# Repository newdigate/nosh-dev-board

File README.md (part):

# Nosh

A development board for the NXP **i.MX RT1176** crossover MCU, modelled closely on the
MIMXRT1170-EVKB (Rev C3) so that EVKB software — `USBHost_t36`, the M2Radio Wi-Fi/BT
library, `MipiDisplay` and the NXP SDK board files — runs with the same pin assignments.
Where Nosh departs from the EVKB it is for JLCPCB availability or because an EVKB block was
not wanted; every departure is listed below.

**Status:** schematic and PCB layout complete (KiCad 10, `Kicad/`): 6-layer JLCPCB stackup, fully
routed, DRC clean with schematic parity. The findings of the 2026-10-28 design review are closed
and merged to `main` on 2026-11-03 (decoupling moved to the chips, DC-jack OVP, reset supervisor,
RTC load caps, MIPI pair matching, ESD on the jacks, P-FET reverse-polarity switch and the rest;
see the git log). ERC is clean apart from the expected unconnected MCU balls and undriven-input
notes on open pins. The JLCPCB order files are in `fab/`; see [Fabrication outputs](#fabrication-outputs).
Ordered 2026-11-03: JLCPCB Y95-2611336A, 5 PCBs + 2 assembled (settings in `fab/README.md`).

## What is on the board

| Block | Choice | Notes |
|---|---|---|
| MCU | MIMXRT1176DVMAA (rev-B DVMAB accepted alternate), MAPBGA-289 | 12-unit symbol generated from `tools/data/*.json`; KiCad stock footprint `Package_BGA:MAPBGA-289_14x14mm_Layout17x17_P0.8mm` (0.32 mm pads, EVKB uses 0.33 mm) |
| SDRAM | 2 × Alliance AS4C32M16SC-7TIN (512 Mb, 133 MHz) on SEMC, 32-bit, **128 MB** | same JEDEC x16 TSOP-54 footprint and arrangement as the EVKB; 13 row × 10 column and a -7 speed grade, so the firmware SEMC setup changes: 10 column bits, 128 MB on chip select 0 and a 132 MHz SEMC clock, see "SDRAM configuration" below |
| Flash | Winbond W25Q512JVEIQ, 512 Mb QSPI, 3.3 V | FlexSPI1 port A (GPIO_SD_B2_06..11) |
| USB2 (OTG2) | micro-AB **host/OTG** port | the port `USBHost_t36` drives; TPS2553 VBUS switch (~1.1 A) with hardware ID gating, RClamp0854P ESD, low-DCR 120 Ω VBUS bead; ≈4.6 V at the connector when sourcing 1 A from the jack |
| USB1 (OTG1) | USB-C **device** port | Rd-only UFP (500 mA), RClamp0854P ESD |
| M.2 Key E | uSDHC1 @ 1.8 V + LPUART2 | for u-blox MAYA-W1 / NXP IW416; 74AVC8T245 level shifters; TE 2199230-4 socket (EVKB part); retention nut H5, M2.5 SMT 2 mm (EVKB BH1) |
| microSD | uSDHC2 @ 3.3 V, TPD1E05U06 ESD diode on each of the six lines | its own bus — the EVKB shares one with the M.2 slot |
| LCD + touch | 40-pin 0.5 mm FPC (Würth 68714014022), MIPI DSI 2 lanes | Rocktech RK055HDMIPI4MA0 (720×1280, HX8394, GT911 touch on LPI2C5), EVKB J48 pinout and GPIO map |
| Audio | NXP SGTL5000 codec (QFN-20) on SAI1 + LPI2C5, 3.5 mm line-out and line-in jacks with TPD1E10B06 bidirectional ESD on the jack side of the coupling caps | the Teensy Audio Shield codec: Teensy Audio library `AudioControlSGTL5000` and the NXP SDK `sgtl5000` driver both apply; I2C 0x0A; same SAI1 pins as the EVKB codec |
| Power | 5 V barrel jack or USB-C → MP2143 3.3 V buck → TLV1117LV 1.8 V; AP2112K SNVS LDO | EVKB-style rail tree, on-chip DCDC for the core; 3 A polyfuse, SMAJ6.0A TVS, IRLML6401 P-FET reverse-polarity switch (gate to GND, ~50 mΩ; replaced the SS54 diode 2026-11-02 to lift the host-port VBUS), TPS259531 eFuse (5.7 V clamp, 3.6 A limit), jack rated 8 A; red power LED on +3V3 |
| Debug | 10-pin 1.27 mm SWD/JTAG header, reset / ONOFF / WAKEUP buttons, 2-way boot-mode DIP, user LED on GPIO_AD_04, 3-pin debug UART header J11 | JTAG on GPIO_LPSR_10..15, VTref = NVCC_LPSR (3.3 V); LPUART1 console on J11 |
| Expansion | none | the 2×10 header J10 was taken off during layout (commit a9f1b1f) to free routing room; see [Expansion header (removed)](#expansion-header-removed) |
| Mechanical | board outline = the RK055HDMIPI4MA0 adapter outline; 4 × M3 mounting holes H1–H4 on the adapter's standoff positions; 6 fiducials, FID1–FID3 on the top side and FID4–FID6 on the bottom for the bottom-side assembly pass | 3.53 mm plated holes with 5.6 mm GND pads (NXP's .635" M3 standoff land, as on the EVKB); hole coordinates from the adapter design files or measurement before layout |

Sheets: `power` (MCU supplies, DCDC, reset/boot), `core` (crystals, USB/MIPI supplies),
`gpio` (GPIO banks, flash, SWD, boot), `usb`, `supply`, `sdram`, `m2`, `sdcard`, `lcd`, `audio`.

## Pin map (for software)

All assignments are the EVKB's unless marked.

| Function | RT1176 pads / balls |
|---|---|
| USB host (OTG2) | USB2_DP/DN C17/C16, VBUS sense D16; `USB_OTG2_ID` GPIO_AD_08, `USB_OTG2_OC` GPIO_AD_06 |
| USB device (OTG1) | USB1_DP/DN E17/E16, VBUS sense D17 |
| M.2 SDIO (uSDHC1, 1.8 V) | GPIO_SD_B1_00..05; `WIFI_RST_B` GPIO_AD_16, `WL_RST_B` GPIO_AD_31, `BT_RST_B` GPIO_AD_15, `WL_DEV_WAKE` GPIO_AD_07, `BT_DEV_WAKE` GPIO_AD_28, `BT_WAKE_B` GPIO_AD_27, `WIFI_WAKE_B` GPIO_AD_29 |
| BT HCI UART (LPUART2) | GPIO_DISP_B2_10..13 |
| microSD (uSDHC2, 3.3 V) — *Nosh* | GPIO_SD_B2_00..05; `SD_CD_B` GPIO_AD_34, `SD_PWREN_B` GPIO_AD_35 |
| QSPI flash (FlexSPI1 A) | GPIO_SD_B2_06..11; read strobe (DQS) on GPIO_EMC_B2_18, see below |
| SDRAM (SEMC) | GPIO_EMC_B1/B2 |
| LCD (MIPI DSI) | D0 A8/B8, D1 A10/B10, CLK A9/B9; reset GPIO_AD_02, backlight GPIO_AD_30, panel power GPIO_DISP_B2_15, TE GPIO_AD_05 |
| Touch + codec I2C (LPI2C5) | GPIO_LPSR_04 SDA / GPIO_LPSR_05 SCL; touch INT GPIO_AD_00, touch RST GPIO_AD_01 |
| Audio (SAI1) | MCLK GPIO_AD_17, RX_SYNC/RX_BCLK GPIO_AD_18/19 (DNP links), RXD0 GPIO_AD_20, TXD0 GPIO_AD_21, TX_BCLK GPIO_AD_22, TX_SYNC GPIO_AD_23 |
| Boot mode | GPIO_LPSR_02/03 (DIP switch, 100 k pull-downs); BOOT_CFG pins GPIO_DISP_B1_06..11 / GPIO_DISP_B2_00..05 pulled down (100 k), so internal boot is from FlexSPI1 QSPI NOR |
| Debug console (LPUART1) | GPIO_AD_24 TXD / GPIO_AD_25 RXD on J11 (1 GND, 2 TXD, 3 RXD) |
| LPSPI3 — *Nosh* | not brought out (J10 removed); GPIO_DISP_B1_06 carries the BT_CFG0 strap (net LPSPI3_SOUT, R92), GPIO_DISP_B1_03..05 are unconnected |
| User LED | GPIO_AD_04 (GPIO9_IO03, the SDK's BOARD_USER_LED), high = on; direct drive, 1 k series, red 0603 (the EVKB buffers it with a BC817) |

## Expansion header (removed)

The 2×10 2.54 mm header J10 (LPUART1, LPI2C5, LPSPI3, FLEXCAN3/LPUART12, four ADC/PWM pins) was
taken off the board during layout (a9f1b1f, schematic cadd849) to free routing room around the
MCU. The pins it used are now unconnected and available if a header is ever added back:
GPIO_AD_10..13, GPIO_AD_26, GPIO_LPSR_00/01 (FLEXCAN3_TX/RX, PDM, MQS) and GPIO_DISP_B1_03..05.
GPIO_DISP_B1_06 (LPSPI3_SOUT) stays a boot strap (BOOT_CFG1[0], R92) and must not be pulled up.
NVCC_DISP1 is still 3.3 V. LPUART1 and LPI2C5 remain reachable on J11 and the LCD/codec nets.

## Differences from the MIMXRT1170-EVKB

| Block | EVKB | Nosh | Why |
|---|---|---|---|
| SDRAM | 2 × W9825G6KH-5I, 64 MB | 2 × AS4C32M16SC-7TIN, 128 MB | pin-compatible 512 Mb parts, 133 MHz (SEMC at 132 instead of 198 MHz); four ordered at JLCPCB on 2026-11-03 (C1349997) after the -6TIN pre-order (C1351095) stayed out of stock. W9825G6KH-6 (C62246, in stock) drops in for 64 MB at 166 MHz |
| USB ports | two micro-AB OTG ports | micro-AB host + USB-C device | one port is enough for the host library; USB-C for programming |
| USB VBUS switch | NX5P3090UK (0.4 mm WLCSP) | TPS2553DBVR (SOT-23-6), RILIM 22 k ≈ 1.1 A | no stock, hard package; same EN/FAULT/ILIM topology |
| SD card bus | shared with the M.2 slot | separate uSDHC2 | independent Wi-Fi and SD |
| M.2 BT HCI UART | needs NXP's "HCI UART rework" (mount the shifter-output 0 R links, cut the shared Arduino / Ethernet-PHY loads, set a jumper) | hard-wired, no rework | see below |
| QSPI flash | W25Q512NWEIQ (1.8 V) | W25Q512JVEIQ (3.3 V) | NVCC_SD2 at 3.3 V keeps the SD bus simple |
| NVCC_DISP1 | 1.8 V (RGMII Ethernet PHY on GPIO_DISP_B1) | 3.3 V | no Ethernet; the bank carries the BOOT_CFG / BT_CFG straps at 3.3 V |
| Boot configuration | DIP switch SW2 + 47 k pull-downs on the 12 BOOT_CFG pins | fixed 100 k pull-downs, no switch | always internal boot from QSPI NOR; reflash through the serial downloader (BOOT_MODE DIP) instead of changing boot devices |
| Arduino headers | four Arduino Uno R3 headers | none (J10 removed during layout) | the Arduino SPI pins (GPIO_AD_28..31) carry the M.2 and backlight signals here |
| LCD backlight / 2.8 V | on-board boost and LDO | none | the RK055HDMIPI4MA0 adapter (NXP SPF-39012) generates its own rails and drives its own backlight from the 5 V on FPC pins 39/40 — keep its jumpers J3/J5/J6 at the default 1-2 |
| LCD TE | 74AVC8T245 level shifter to GPIO_AD_05 | DNP 0 R | DSI video mode never uses TE; add a shifter if needed |
| Audio | WM8962 (0.5 mm WLCSP-49) with speaker outputs, electret mic and headphone jack with detect | SGTL5000 (QFN-20) with line out and line in | Teensy Audio library support; the QFN routes on standard 6-layer rules where the WLCSP needed via-in-pad; no mic, speakers or jack detect wanted |
| Not fitted at all | Ethernet (1G + 100M), CAN transceivers, camera, PMIC, LPC55 debug probe, PDM mics, accelerometer | — | use an external SWD probe; the FLEXCAN3 / PDM pins (GPIO_LPSR_00/01) are unconnected |

**No M.2 HCI UART rework.** NXP's EdgeFast Bluetooth
[hardware rework guide](https://mcuxpresso.nxp.com/mcuxsdk/25.09.00/html/middleware/edgefast_bluetooth/docs/HWRGEFBTPALUG/topics/RT1170EVKB_Murata_M2.html)
makes the EVKB + Murata M.2 combination work by mounting resistors, removing one and setting jumpers
(its designators are from an earlier EVKB build; on the RevC3 files the module-to-MCU UART_RXD/UART_CTS
links are R1901/R1902, 0 R DNP, and LPUART2's pins are shared with the Arduino header, the J57 FFC and
the Ethernet PHY reset/interrupt). Nosh needs none of it: GPIO_DISP_B2_10..13 run point-to-point through
U11/U12 (OE grounded, DIR fixed) to M.2 pins 32/22/36/34 with no 0 R links, no DNP parts and no other
loads, with the EVKB's pin mapping, so the SDK's LPUART2 flow-control setup applies unchanged. The guide's
PCM rework does not apply either: the M.2 PCM/I2S pins (8, 10, 12, 14) are not connected, so A2DP over
HCI works but HFP voice over the PCM path is not possible without a board change.

## Sourcing / BOM

The board is intended for JLCPCB assembly. Every component carries hidden `LCSC` and `MPN`
fields (U1 also `MPN_Alt`/`LCSC_Alt`), and `Kicad/tools/data/lcsc_parts.csv` is the generated
summary: one line per order code with quantity and references, DNP parts marked. Current count
(2026-11-03): 268 fitted parts on 70 order codes, 24 of them JLCPCB *Basic*; 8 DNP parts. Regenerate
it with

```bash
python3 Kicad/tools/lcsc_table.py
```

### Fabrication outputs

`fab/` holds the JLCPCB order files, regenerated from the board with

```bash
python3 Kicad/tools/fab_export.py
```

(`--no-tht` leaves the two through-hole parts, J4 and J11, off the BOM and CPL for hand soldering).
It writes `Nosh-gerbers.zip` (6 copper layers, paste, silk, mask, edge cuts, one Excellon drill
file with its map), `Nosh-bom.csv` and `Nosh-cpl.csv` in JLCPCB's column formats, and
`fab/README.md` with the order settings (6 layers, 1.6 mm, ENIG, epoxy-filled-and-capped vias for
the via-in-pad caps, both-side assembly, stencil, BGA X-ray) and the export summary. Before paying:
consign or reserve U1 and the U9/U10 SDRAM (JLCPCB stock 0), export the position file with DNP
excluded (the script does), and check every polarised part's rotation in JLCPCB's placement
preview, since the CPL carries KiCad rotations. No impedance control was computed for the USB
and MIPI pairs; order it on JLC06161H-3313 or accept the 0.13 mm / 0.11–0.13 mm geometry as is.

### MCU availability (read before ordering)

- NXP moved the whole i.MX RT1170 family to rev-B silicon in March 2025 (PCN 202502019I,
  suffix `A` → `B`, fixes erratum ERR052351). The rev-A **MIMXRT1176DVMAA** used here is now
  *Not Recommended for New Designs*, but it is the EVKB part and the only one actually
  obtainable in small quantities (Digi-Key stock; JLCPCB has only a handful).
- **MIMXRT1176DVMAB** (rev B) is pin-identical and is the **accepted alternate**: fit either.
  As of Oct 2026 it has no distributor stock and a ~39-week lead time.
- Buy the MCU yourself (Digi-Key/Mouser) and consign it to JLCPCB rather than relying on
  JLCPCB's own stock. Only the 0–95 °C "D" grade is the 1 GHz bin; the industrial C/A grades
  are 800 MHz parts and need a clock-init change if ever fitted.

### Other parts worth checking before an order

| Part | JLCPCB | Oct 2026 stock | Alternative |
|---|---|---|---|
| SGTL5000XNLA3R2 codec | C2651833 | ~1.1 k | CS4272 (TSSOP-28, Teensy driver, line level only, 5 V analog) |
| Würth 68714014022 LCD FPC | C6264899 | ~75 | any 40-pin 0.5 mm top-contact ZIF with the same land pattern |
| Same Sky (CUI) SJ-3524-SMT jacks J8/J9 | C20182907 | ~800 | SJ-3523-SMT (C4991872, same pads minus the TN switch pad) when it is back in stock; SHOU HAN PJ-320D (C431535, ~70 k) needs a new footprint |
| TE 2199230-4 M.2 socket | C2977809 | ~5 k | — |
| AS4C32M16SC-7TIN SDRAM U9/U10 | C1349997 | 13 (four ordered 2026-11-03); the -6TIN (C1351095) stayed at 0 | W9825G6KH-6 (C62246, 61) or W9825G6KH-6I (C97572, 267): 256 Mb, 64 MB total, SEMC COL=9, 166 MHz. W989D6DBGX6I (C2641243, 8 k) is a 512 Mb 1.8 V LPSDR in VFBGA-54: only for a re-layout |
| YIYUAN SMTSOM2.520BTR M.2 nut H5, 2 mm | C5301776 | 0 | SMTSOM2.525BTR, 2.5 mm (C49236513, ~4.7 k): same land, the card end sits 0.5 mm higher |

Fine-pitch note: the MCU is 0.8 mm BGA; everything else is 0.4 mm QFN or coarser.

## Flashing and debugging

The RT1176 has no internal flash: the ROM boots from the W25Q512 on FlexSPI1, so "flashing"
means writing the QSPI NOR through the MCU. A debug tool needs an RT1170 FlexSPI flash
algorithm (it loads a small loader into OCRAM that uses the ROM's FlexSPI API); pyOCD gets it
from the NXP CMSIS pack, J-Link has it built in. Images must start with the FCB + IVT + boot
data at `0x30000000` — any SDK `flexspi_nor` link target does this, and the EVKB FCB (written
for the 1.8 V W25Q512NW) drives our 3.3 V W25Q512JV unchanged (same command set, same QE bit).

### SWD header J1 (standard Cortex 10-pin, 1.27 mm)

| Pin | Signal | Pin | Signal |
|---|---|---|---|
| 1 | VTref = NVCC_LPSR (3.3 V) | 2 | SWDIO (GPIO_LPSR_15) |
| 3 | GND | 4 | SWCLK (GPIO_LPSR_14) |
| 5 | GND | 6 | SWO (GPIO_LPSR_11) |
| 7 | key | 8 | TDI (GPIO_LPSR_12) |
| 9 | GND | 10 | nRESET → POR_B via D1 |

JTAG_MOD is pulled low (SWD mode) and the debug domain is 3.3 V, so any 3.3 V SWD probe
connects directly.

### Serial console J11 (0.1" 1x3)

| Pin | Signal | Connect to |
|---|---|---|
| 1 | GND | adapter GND |
| 2 | LPUART1_TXD (GPIO_AD_24), board output | adapter RX |
| 3 | LPUART1_RXD (GPIO_AD_25), board input | adapter TX |

3.3 V levels, so use a 3.3 V USB-serial adapter. LPUART1 is the SDK's default debug console,
usually 115200 8N1.

### Probes

- Any **CMSIS-DAP** probe: NXP MCU-Link (the EVKB's own probe as a dongle; also works with
  LinkServer/MCUXpresso), Raspberry Pi Debug Probe (CMSIS-DAP v2, fast), Atmel-ICE (its EDBG
  firmware exposes a standard CMSIS-DAP interface; use the 10-pin "SAM" header), or a SAMD21
  board such as a MKR ZERO running [free-dap](https://github.com/ataradov/free-dap) (slow HID
  probe, fine for bring-up; wire SWCLK, SWDIO, GND and optionally nRESET).
- **J-Link**: `-device MIMXRT1176xxxA_M7 -if SWD`; the most robust RT1170 flash loader.
- AVR-only programmers (AVRISP mkII, STK500, UPDI) cannot do SWD.

### pyOCD (generic CMSIS-DAP probes)

```bash
pip install pyocd
pyocd pack install mimxrt1176          # NXP MIMXRT1176 DFP incl. the FlexSPI NOR algorithm
pyocd list --targets | grep -i 1176    # pick the ..._cm7 target the pack installed
pyocd flash -t <target> -f 4m app.elf  # or app.bin -a 0x30000000
pyocd gdbserver -t <target>
```

If the flash is blank or holds a bad image the ROM may sit in its serial-downloader loop; add
`--connect under-reset` if a plain attach fails. OpenOCD has no mainline RT1170 FlexSPI
driver, so pyOCD is the practical choice for generic probes.

### No probe: the ROM serial downloader over USB-C

Set the boot DIP to `01` (serial downloader) and plug the USB-C port — it is USB1/OTG1, the
port the RT1170 ROM uses for SDP. Then with NXP's SPSDK:

```bash
pip install spsdk
nxpdevscan                                                   # ROM enumerates as 1fc9:013d
blhost -u 0x1fc9,0x013d -- load-image ivt_flashloader.bin    # from the RT1170 SDK / SPT package
blhost -u 0x15a2,0x0073 -- fill-memory 0x2000 4 0xC0000007   # QuadSPI NOR config option
blhost -u 0x15a2,0x0073 -- configure-memory 9 0x2000
blhost -u 0x15a2,0x0073 -- flash-erase-region 0x30000000 0x100000 9
blhost -u 0x15a2,0x0073 -- write-memory 0x30000000 app.bin
```

NXP's MCUXpresso Secure Provisioning Tool does the same through a GUI. This is also the
recovery path if a bad image ever makes an SWD attach awkward.

### Test points

Seven bare pads for bring-up, none in the BOM or placement files (`Nosh:TestPoint_*_JLC` footprints,
the KiCad ones without the silk ring that would break JLCPCB's 0.15 mm silk-to-pad rule):

| Ref | Net | Where | Pad |
|---|---|---|---|
| TP1 | GND | west edge by J4 (18.0, 63.0) | 2.0 mm plated hole, solder a wire loop for the scope ground |
| TP2 | GND | south of U16 / SW1 (104.0, 56.0) | 2.0 mm plated hole |
| TP3 | +5V | by J4 (17.5, 60.0) | 1.0 mm pad on a via into the +5V plane |
| TP4 | +3V3 | (25.0, 60.5) | 1.0 mm pad on a via into the +3V3 plane |
| TP5 | +1V8 | east of U8 (44.7, 65.1) | 1.0 mm pad |
| TP6 | DCDC_DIG | **bottom side**, beside C31 under U1 (73.3, 61.5) | 1.0 mm pad |
| TP7 | POR_B | south-east of U16 (109.3, 55.5) | 1.0 mm pad |

The 72 test points of the first layout were removed with J10 (a9f1b1f). SWD/SWO are on J1, the LPUART1
console on J11 (GPIO_AD_24/25, 3.3 V). Nothing is probed on the SDRAM, FlexSPI, USB data, MIPI DSI or
crystal nets, where a pad stub would degrade the signal.

### SDRAM configuration: 10 column address bits, not 9

The EVKB's W9825G6KH (256 Mb, 16M × 16) has 13 row × 9 column bits per bank. Nosh's AS4C32M16SC
(512 Mb, 32M × 16) has 13 row × **10** column bits per bank, the same 4 banks and the same A0–A12
pins (A12 on pin 36). The hardware is identical; only the SEMC setup differs. Every EVKB-derived
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
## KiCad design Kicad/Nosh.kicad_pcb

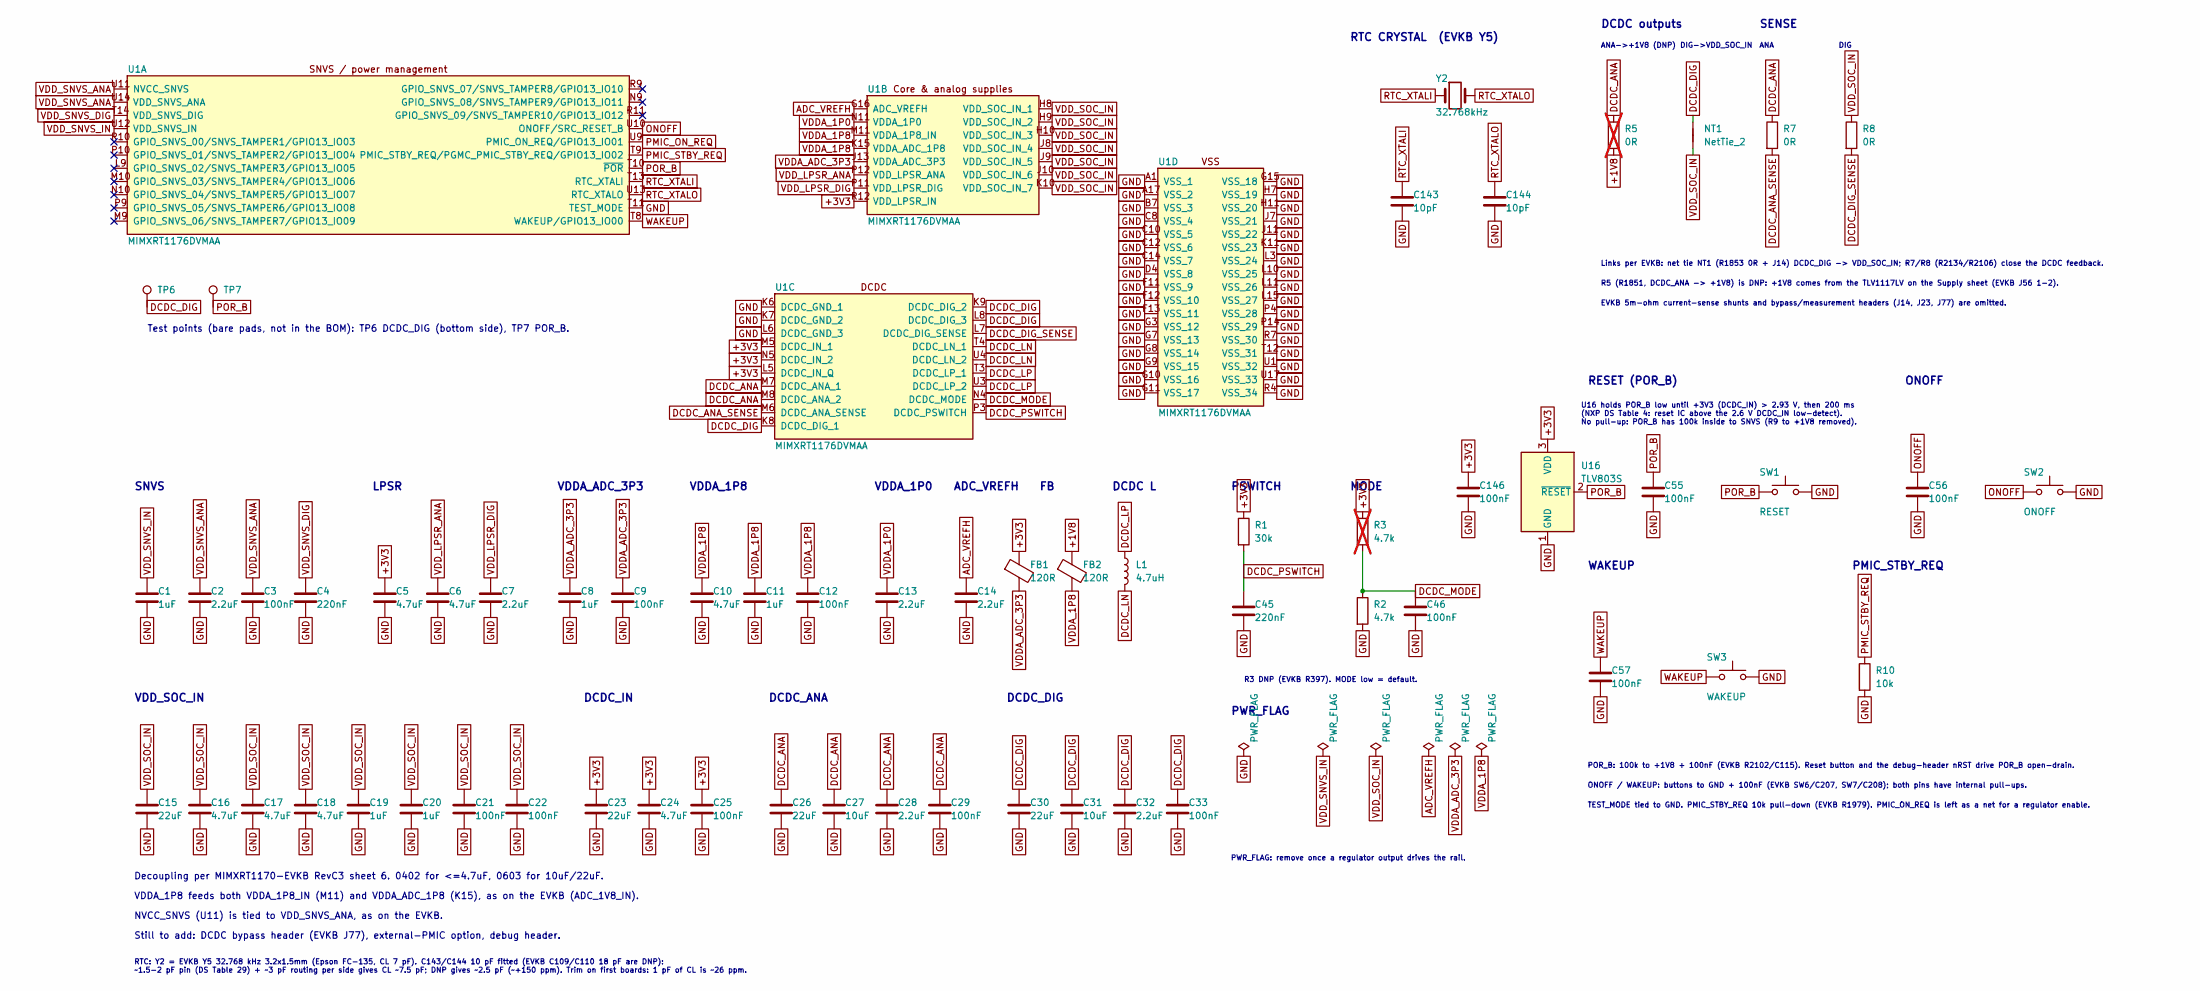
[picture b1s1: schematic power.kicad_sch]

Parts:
C1, C8: 1uF; C_0402_1005Metric_JLC; MPN CL05A105KA5NQNC; LCSC C52923
C2, C13, C14: 2.2uF; C_0402_1005Metric_JLC; MPN CL05A225MQ5NSNC; LCSC C12530
C3, C12, C21, C25, C33: 100nF; C_0402_1005Metric_ViP; MPN CL05B104KO5NNNC; LCSC C1525
C4, C45: 220nF; C_0402_1005Metric_JLC; MPN CL05B224KO5NNNC; LCSC C16772
C5, C16, C17, C24: 4.7uF; C_0402_1005Metric_ViP; MPN CL05A475MP5NRNC; LCSC C23733
C6, C10, C18: 4.7uF; C_0402_1005Metric_JLC; MPN CL05A475MP5NRNC; LCSC C23733
C7, C28, C32: 2.2uF; C_0402_1005Metric_ViP; MPN CL05A225MQ5NSNC; LCSC C12530
C9, C22, C29, C46, C55, C56, C57, C146: 100nF; C_0402_1005Metric_JLC; MPN CL05B104KO5NNNC; LCSC C1525
C11, C19, C20: 1uF; C_0402_1005Metric_ViP; MPN CL05A105KA5NQNC; LCSC C52923
C15, C23, C26, C30: 22uF; C_0603_1608Metric; MPN CL10A226MQ8NRNC; LCSC C59461
C27, C31: 10uF; C_0603_1608Metric; MPN CL10A106KP8NNNC; LCSC C19702
C143, C144: 10pF; C_0402_1005Metric_JLC; MPN CL05C100JB5NNNC; LCSC C32949
FB1, FB2: 120R; L_0402_1005Metric; MPN BLM15AG121SN1D; LCSC C85812
L1: 4.7uH; L_APV_ANR4020; MPN ANR4020T4R7M; LCSC C6364800
NT1: NetTie_2; NetTie-2_SMD_0805
R1: 30k; R_0402_1005Metric_JLC; MPN FRC0402F3002TS; LCSC C2909347
R2: 4.7k; R_0402_1005Metric_JLC; MPN 0402WGF4701TCE; LCSC C25900
R3: 4.7k; R_0402_1005Metric_JLC; MPN 0402WGF4701TCE; LCSC C25900; not fitted
R5: 0R; R_0805_2012Metric; MPN 0805W8F0000T5E; LCSC C17477; not fitted
R7, R8: 0R; R_0402_1005Metric_JLC; MPN 0402WGF0000TCE; LCSC C17168
R10: 10k; R_0402_1005Metric_JLC; MPN 0402WGF1002TCE; LCSC C25744
SW1: RESET; SW_SPST_B3U-1000P; MPN B3U-1000P; LCSC C231329
SW2: ONOFF; SW_SPST_B3U-1000P; MPN B3U-1000P; LCSC C231329
SW3: WAKEUP; SW_SPST_B3U-1000P; MPN B3U-1000P; LCSC C231329
TP6, TP7: TestPoint; TestPoint_Pad_D1.0mm_JLC
U1: MIMXRT1176DVMAA; MAPBGA-289_14x14mm_Layout17x17_P0.8mm; MPN MIMXRT1176DVMAA; LCSC C1020237
U16: TLV803S; SOT-23; MPN TLV803SDBZR; LCSC C132016
Y2: 32.768kHz; Crystal_SMD_3215-2Pin_3.2x1.5mm_JLC; MPN Q13FC13500002; LCSC C48615

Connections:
+1V8: FB2.1, R5.2; also elsewhere on the board
+3V3: C5.1, C23.1, C24.1, C25.1, C146.1, FB1.1, R1.1, R3.1, U1.L5 (DCDC_IN_Q), U1.M5 (DCDC_IN_1), U1.N5 (DCDC_IN_2), U1.R12 (VDD_LPSR_IN), U16.3 (VDD); also elsewhere on the board
ADC_VREFH: C14.1, U1.G16 (ADC_VREFH); also elsewhere on the board
DCDC_ANA: C26.1, C27.1, C28.1, C29.1, R5.1, R7.1, U1.M7 (DCDC_ANA_1), U1.M8 (DCDC_ANA_2)
DCDC_ANA_SENSE: R7.2, U1.M6 (DCDC_ANA_SENSE)
DCDC_DIG: C30.1, C31.1, C32.1, C33.1, NT1.1, TP6.1, U1.K8 (DCDC_DIG_1), U1.K9 (DCDC_DIG_2), U1.L8 (DCDC_DIG_3)
DCDC_DIG_SENSE: R8.2, U1.L7 (DCDC_DIG_SENSE)
DCDC_LN: L1.2, U1.T4 (DCDC_LN_1), U1.U4 (DCDC_LN_2)
DCDC_LP: L1.1, U1.T3 (DCDC_LP_1), U1.U3 (DCDC_LP_2)
DCDC_MODE: C46.1, R2.1, R3.2, U1.N4 (DCDC_MODE)
DCDC_PSWITCH: C45.1, R1.2, U1.P3 (DCDC_PSWITCH)
GND: C1.2, C2.2, C3.2, C4.2, C5.2, C6.2, C7.2, C8.2, C9.2, C10.2, C11.2, C12.2, C13.2, C14.2, C15.2, C16.2, C17.2, C18.2, C19.2, C20.2, C21.2, C22.2, C23.2, C24.2, C25.2, C26.2, C27.2, C28.2, C29.2, C30.2, C31.2, C32.2, C33.2, C45.2, C46.2, C55.2, C56.2, C57.2, C143.2, C144.2, C146.2, R2.2, R10.2, SW1.2, SW2.2, SW3.2, U1.A1 (VSS_1), U1.A17 (VSS_2), U1.B7 (VSS_3), U1.C8 (VSS_4), U1.C10 (VSS_5), U1.C12 (VSS_6), U1.C14 (VSS_7), U1.D4 (VSS_8), U1.F11 (VSS_9), U1.F12 (VSS_10), U1.F13 (VSS_11), U1.G3 (VSS_12), U1.G7 (VSS_13), U1.G8 (VSS_14), U1.G9 (VSS_15), U1.G10 (VSS_16), U1.G11 (VSS_17), U1.G15 (VSS_18), U1.H7 (VSS_19), U1.H11 (VSS_20), U1.J7 (VSS_21), U1.J11 (VSS_22), U1.K6 (DCDC_GND_1), U1.K7 (DCDC_GND_2), U1.K11 (VSS_23), U1.L3 (VSS_24), U1.L6 (DCDC_GND_3), U1.L10 (VSS_25), U1.L11 (VSS_26), U1.L15 (VSS_27), U1.P4 (VSS_28), U1.P14 (VSS_29), U1.R4 (VSS_34), U1.R7 (VSS_30), U1.T11 (TEST_MODE), U1.T12 (VSS_31), U1.U1 (VSS_32), U1.U17 (VSS_33), U16.1 (GND); also elsewhere on the board
ONOFF: C56.1, SW2.1, U1.U10 (ONOFF/SRC_RESET_B)
PMIC_ON_REQ: U1.U9 (PMIC_ON_REQ/GPIO13_IO01); also elsewhere on the board
PMIC_STBY_REQ: R10.1, U1.T9 (PMIC_STBY_REQ/PGMC_PMIC_STBY_REQ/GPIO13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)
POR_B: C55.1, SW1.1, TP7.1, U1.T10 (~POR), U16.2 (~RESET); also elsewhere on the board
RTC_XTALI: C143.1, U1.T13 (RTC_XTALI), Y2.1
RTC_XTALO: C144.1, U1.U13 (RTC_XTALO), Y2.2
VDDA_1P0: C13.1, U1.N11 (VDDA_1P0); also elsewhere on the board
VDDA_1P8: C10.1, C11.1, C12.1, FB2.2, U1.K15 (VDDA_ADC_1P8), U1.M11 (VDDA_1P8_IN)
VDDA_ADC_3P3: C8.1, C9.1, FB1.2, U1.J13 (VDDA_ADC_3P3)
VDD_LPSR_ANA: C6.1, U1.P12 (VDD_LPSR_ANA)
VDD_LPSR_DIG: C7.1, U1.P11 (VDD_LPSR_DIG)
VDD_SNVS_ANA: C2.1, C3.1, U1.U11 (NVCC_SNVS), U1.U14 (VDD_SNVS_ANA)
VDD_SNVS_DIG: C4.1, U1.T14 (VDD_SNVS_DIG)
VDD_SNVS_IN: C1.1, U1.U12 (VDD_SNVS_IN); also elsewhere on the board
VDD_SOC_IN: C15.1, C16.1, C17.1, C18.1, C19.1, C20.1, C21.1, C22.1, NT1.2, R8.1, U1.H8 (VDD_SOC_IN_1), U1.H9 (VDD_SOC_IN_2), U1.H10 (VDD_SOC_IN_3), U1.J8 (VDD_SOC_IN_4), U1.J9 (VDD_SOC_IN_5), U1.J10 (VDD_SOC_IN_6), U1.K10 (VDD_SOC_IN_7)
WAKEUP: C57.1, SW3.1, U1.T8 (WAKEUP/GPIO13_IO00)

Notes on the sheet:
DIG
SNVS
R5 (R1851, DCDC_ANA -> +1V8) is DNP: +1V8 comes from the TLV1117LV on the Supply sheet (EVKB J56 1-2).
ANA->+1V8 (DNP)
WAKEUP
RTC: Y2 = EVKB Y5 32.768 kHz 3.2x1.5mm (Epson FC-135, CL 7 pF). C143/C144 10 pF fitted (EVKB C109/C110 18 pF are DNP): ~1.5-2 pF pin (DS Table 29) + ~3 pF routing per side gives CL ~7.5 pF; DNP gives ~2.5 pF (~+150 ppm). Trim on first boards: 1 pF of CL is ~26 ppm.
U16 holds POR_B low until +3V3 (DCDC_IN) > 2.93 V, then 200 ms (NXP DS Table 4: reset IC above the 2.6 V DCDC_IN low-detect). No pull-up: POR_B has 100k inside to SNVS (R9 to +1V8 removed).
PWR_FLAG: remove once a regulator output drives the rail.
DCDC L
VDDA_1P8 feeds both VDDA_1P8_IN (M11) and VDDA_ADC_1P8 (K15), as on the EVKB (ADC_1V8_IN).
VDDA_1P0
TEST_MODE tied to GND. PMIC_STBY_REQ 10k pull-down (EVKB R1979). PMIC_ON_REQ is left as a net for a regulator enable.
PMIC_STBY_REQ
R3 DNP (EVKB R397). MODE low = default.
ADC_VREFH
SENSE
Still to add: DCDC bypass header (EVKB J77), external-PMIC option, debug header.
DCDC outputs
DCDC_DIG
VDDA_ADC_3P3
PSWITCH
VDDA_1P8
DCDC_IN
LPSR
ANA
RTC CRYSTAL (EVKB Y5)
MODE
RESET (POR_B)
EVKB 5m-ohm current-sense shunts and bypass/measurement headers (J14, J23, J77) are omitted.
PWR_FLAG
POR_B: 100k to +1V8 + 100nF (EVKB R2102/C115). Reset button and the debug-header nRST drive POR_B open-drain.
NVCC_SNVS (U11) is tied to VDD_SNVS_ANA, as on the EVKB.
Links per EVKB: net tie NT1 (R1853 0R + J14) DCDC_DIG -> VDD_SOC_IN; R7/R8 (R2134/R2106) close the DCDC feedback.
VDD_SOC_IN
DCDC_ANA
ONOFF / WAKEUP: buttons to GND + 100nF (EVKB SW6/C207, SW7/C208); both pins have internal pull-ups.
ONOFF
Decoupling per MIMXRT1170-EVKB RevC3 sheet 6. 0402 for <=4.7uF, 0603 for 10uF/22uF.
DIG->VDD_SOC_IN
Test points (bare pads, not in the BOM): TP6 DCDC_DIG (bottom side), TP7 POR_B.

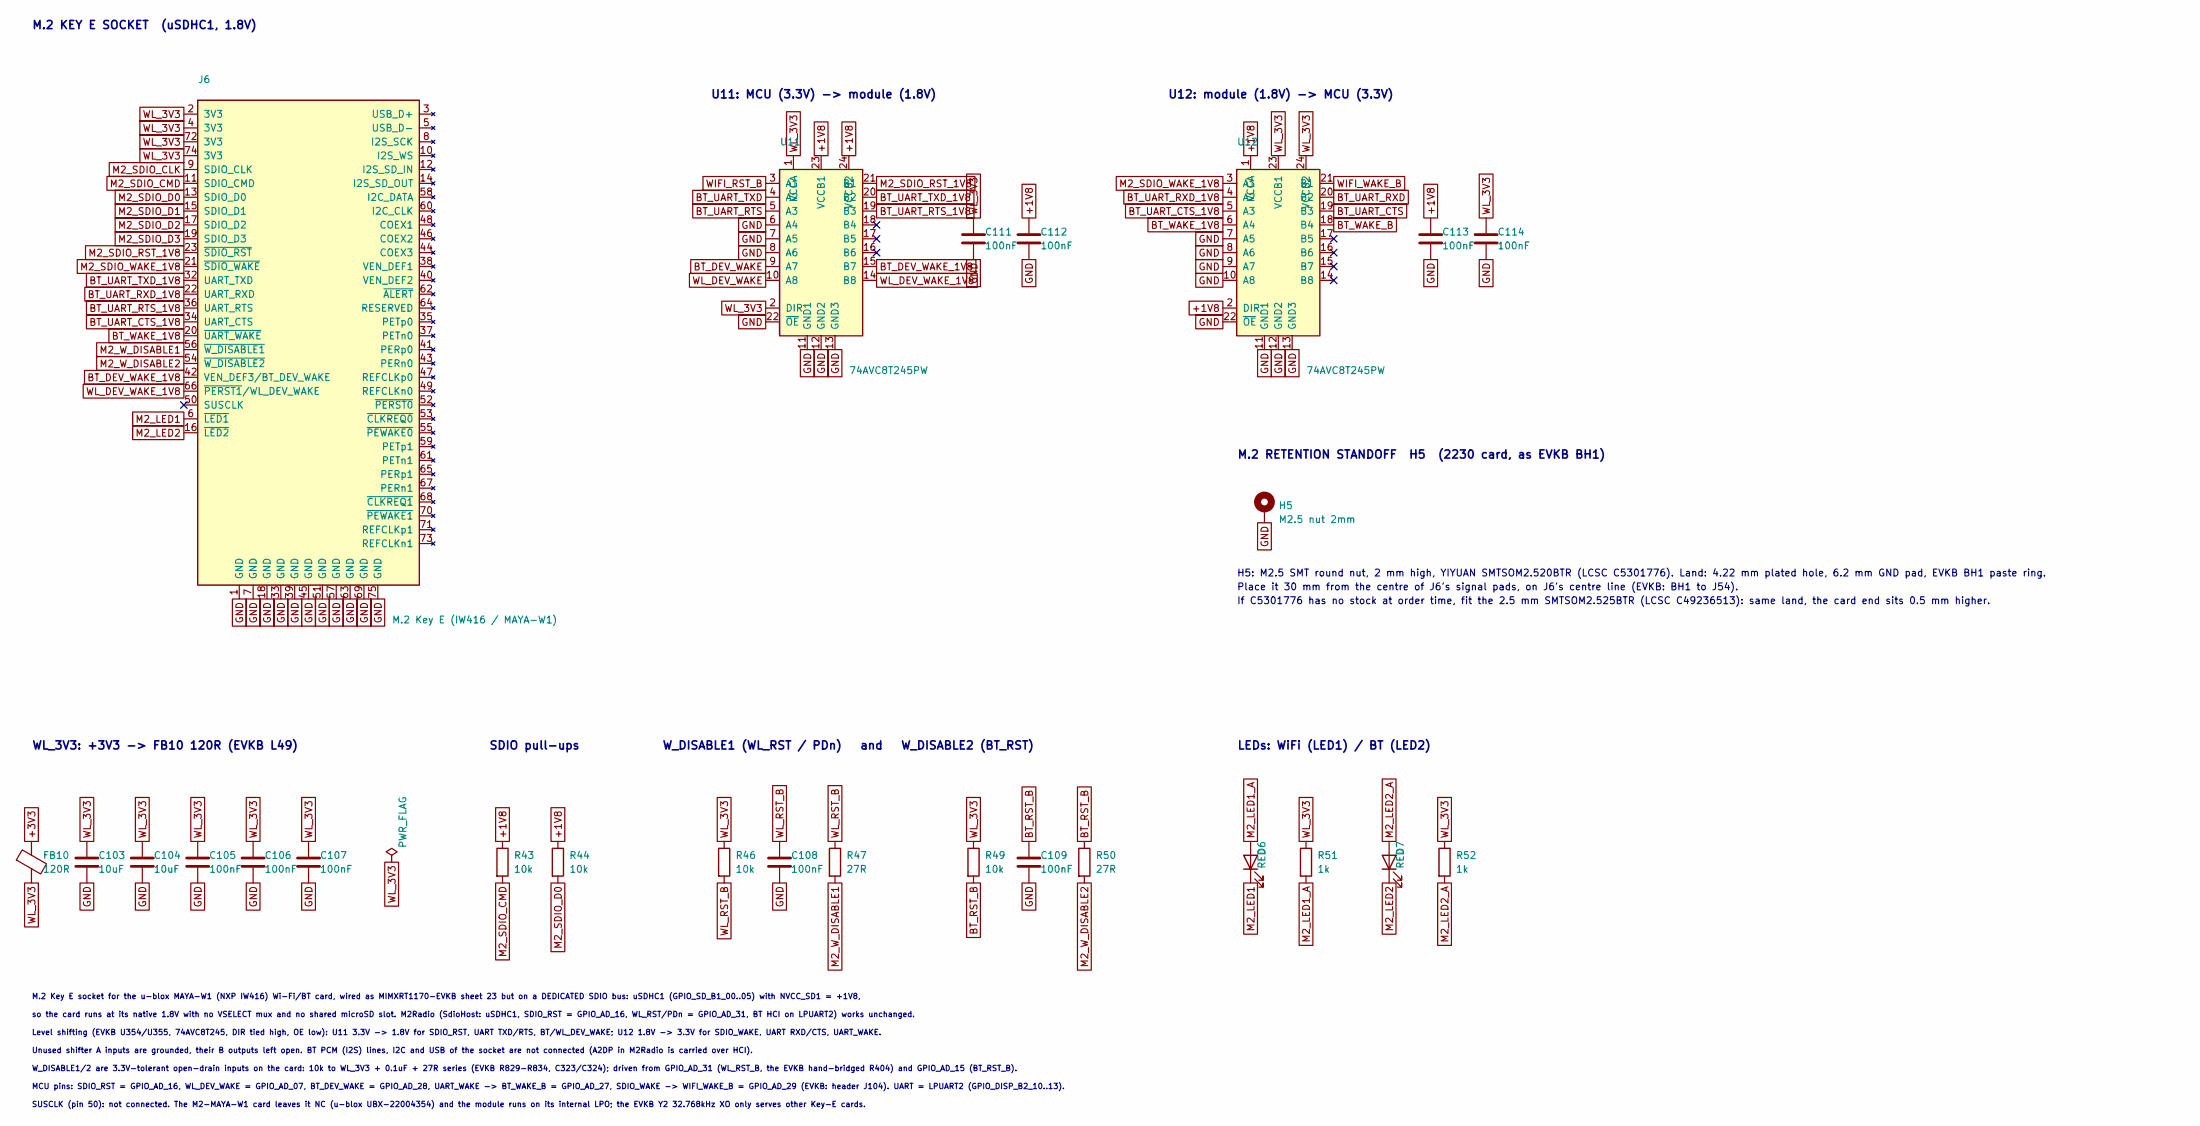
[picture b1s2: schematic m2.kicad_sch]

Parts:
C103, C104: 10uF; C_0603_1608Metric; MPN CL10A106KP8NNNC; LCSC C19702
C105, C106, C107, C108, C109, C111, C112, C113, C114: 100nF; C_0402_1005Metric_JLC; MPN CL05B104KO5NNNC; LCSC C1525
D6, D7: RED; LED_0603_1608Metric; MPN KT-0603R; LCSC C2286
FB10: 120R; L_0603_1608Metric; MPN BLM18PG121SN1D; LCSC C14709
H5: M2.5 nut 2mm; SMTSO_M2.5_Hole4.22mm_Pad6.2mm; MPN SMTSOM2.520BTR; LCSC C5301776
J6: M.2 Key E (IW416 / MAYA-W1); M2_KeyE_67pin_RA; MPN 2199230-4; LCSC C2977809
R43, R44, R46, R49: 10k; R_0402_1005Metric_JLC; MPN 0402WGF1002TCE; LCSC C25744
R47, R50: 27R; R_0402_1005Metric_JLC; MPN 0402WGF270JTCE; LCSC C25100
R51, R52: 1k; R_0402_1005Metric_JLC; MPN 0402WGF1001TCE; LCSC C11702
U11, U12: 74AVC8T245PW; TSSOP-24_4.4x7.8mm_P0.65mm; MPN SN74AVC8T245PWR; LCSC C465742

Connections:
+1V8: C112.1, C113.1, R43.1, R44.1, U11.23 (VCCB1), U11.24 (VCCB2), U12.1 (VCCA), U12.2 (DIR); also elsewhere on the board
+3V3: FB10.1; also elsewhere on the board
BT_DEV_WAKE: U11.9 (A7); also elsewhere on the board
BT_DEV_WAKE_1V8: J6.42 (VEN_DEF3/BT_DEV_WAKE), U11.15 (B7)
BT_RST_B: C109.1, R49.2, R50.1; also elsewhere on the board
BT_UART_CTS: U12.19 (B3); also elsewhere on the board
BT_UART_CTS_1V8: J6.34 (UART_CTS), U12.5 (A3)
BT_UART_RTS: U11.5 (A3); also elsewhere on the board
BT_UART_RTS_1V8: J6.36 (UART_RTS), U11.19 (B3)
BT_UART_RXD: U12.20 (B2); also elsewhere on the board
BT_UART_RXD_1V8: J6.22 (UART_RXD), U12.4 (A2)
BT_UART_TXD: U11.4 (A2); also elsewhere on the board
BT_UART_TXD_1V8: J6.32 (UART_TXD), U11.20 (B2)
BT_WAKE_1V8: J6.20 (~UART_WAKE), U12.6 (A4)
BT_WAKE_B: U12.18 (B4); also elsewhere on the board
GND: C103.2, C104.2, C105.2, C106.2, C107.2, C108.2, C109.2, C111.2, C112.2, C113.2, C114.2, H5.1, J6.1 (GND), J6.7 (GND), J6.18 (GND), J6.33 (GND), J6.39 (GND), J6.45 (GND), J6.51 (GND), J6.57 (GND), J6.63 (GND), J6.69 (GND), J6.75 (GND), U11.6 (A4), U11.7 (A5), U11.8 (A6), U11.11 (GND1), U11.12 (GND2), U11.13 (GND3), U11.22 (~OE), U12.7 (A5), U12.8 (A6), U12.9 (A7), U12.10 (A8), U12.11 (GND1), U12.12 (GND2), U12.13 (GND3), U12.22 (~OE); also elsewhere on the board
M2_LED1: D6.1 (K), J6.6 (~LED1)
M2_LED1_A: D6.2 (A), R51.2
M2_LED2: D7.1 (K), J6.16 (~LED2)
M2_LED2_A: D7.2 (A), R52.2
M2_SDIO_CLK: J6.9 (SDIO_CLK); also elsewhere on the board
M2_SDIO_CMD: J6.11 (SDIO_CMD), R43.2; also elsewhere on the board
M2_SDIO_D0: J6.13 (SDIO_D0), R44.2; also elsewhere on the board
M2_SDIO_D1: J6.15 (SDIO_D1); also elsewhere on the board
M2_SDIO_D2: J6.17 (SDIO_D2); also elsewhere on the board
M2_SDIO_D3: J6.19 (SDIO_D3); also elsewhere on the board
M2_SDIO_RST_1V8: J6.23 (~SDIO_RST), U11.21 (B1)
M2_SDIO_WAKE_1V8: J6.21 (~SDIO_WAKE), U12.3 (A1)
M2_W_DISABLE1: J6.56 (~W_DISABLE1), R47.2
M2_W_DISABLE2: J6.54 (~W_DISABLE2), R50.2
WIFI_RST_B: U11.3 (A1); also elsewhere on the board
WIFI_WAKE_B: U12.21 (B1); also elsewhere on the board
WL_3V3: C103.1, C104.1, C105.1, C106.1, C107.1, C111.1, C114.1, FB10.2, J6.2 (3V3), J6.4 (3V3), J6.72 (3V3), J6.74 (3V3), R46.1, R49.1, R51.1, R52.1, U11.1 (VCCA), U11.2 (DIR), U12.23 (VCCB1), U12.24 (VCCB2)
WL_DEV_WAKE: U11.10 (A8); also elsewhere on the board
WL_DEV_WAKE_1V8: J6.66 (~PERST1/WL_DEV_WAKE), U11.14 (B8)
WL_RST_B: C108.1, R46.2, R47.1; also elsewhere on the board

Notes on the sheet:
LEDs: WiFi (LED1) / BT (LED2)
Unused shifter A inputs are grounded, their B outputs left open. BT PCM (I2S) lines, I2C and USB of the socket are not connected (A2DP in M2Radio is carried over HCI).
WL_3V3: +3V3 -> FB10 120R (EVKB L49)
If C5301776 has no stock at order time, fit the 2.5 mm SMTSOM2.525BTR (LCSC C49236513): same land, the card end sits 0.5 mm higher.
Place it 30 mm from the centre of J6's signal pads, on J6's centre line (EVKB: BH1 to J54).
so the card runs at its native 1.8V with no VSELECT mux and no shared microSD slot. M2Radio (SdioHost: uSDHC1, SDIO_RST = GPIO_AD_16, WL_RST/PDn = GPIO_AD_31, BT HCI on LPUART2) works unchanged.
W_DISABLE1/2 are 3.3V-tolerant open-drain inputs on the card: 10k to WL_3V3 + 0.1uF + 27R series (EVKB R829-R834, C323/C324); driven from GPIO_AD_31 (WL_RST_B, the EVKB hand-bridged R404) and GPIO_AD_15 (BT_RST_B).
M.2 RETENTION STANDOFF H5 (2230 card, as EVKB BH1)
U12: module (1.8V) -> MCU (3.3V)
Level shifting (EVKB U354/U355, 74AVC8T245, DIR tied high, OE low): U11 3.3V -> 1.8V for SDIO_RST, UART TXD/RTS, BT/WL_DEV_WAKE; U12 1.8V -> 3.3V for SDIO_WAKE, UART RXD/CTS, UART_WAKE.
SUSCLK (pin 50): not connected. The M2-MAYA-W1 card leaves it NC (u-blox UBX-22004354) and the module runs on its internal LPO; the EVKB Y2 32.768kHz XO only serves other Key-E cards.
M.2 Key E socket for the u-blox MAYA-W1 (NXP IW416) Wi-Fi/BT card, wired as MIMXRT1170-EVKB sheet 23 but on a DEDICATED SDIO bus: uSDHC1 (GPIO_SD_B1_00..05) with NVCC_SD1 = +1V8,
U11: MCU (3.3V) -> module (1.8V)
M.2 KEY E SOCKET (uSDHC1, 1.8V)
H5: M2.5 SMT round nut, 2 mm high, YIYUAN SMTSOM2.520BTR (LCSC C5301776). Land: 4.22 mm plated hole, 6.2 mm GND pad, EVKB BH1 paste ring.
MCU pins: SDIO_RST = GPIO_AD_16, WL_DEV_WAKE = GPIO_AD_07, BT_DEV_WAKE = GPIO_AD_28, UART_WAKE -> BT_WAKE_B = GPIO_AD_27, SDIO_WAKE -> WIFI_WAKE_B = GPIO_AD_29 (EVKB: header J104). UART = LPUART2 (GPIO_DISP_B2_10..13).
SDIO pull-ups
W_DISABLE1 (WL_RST / PDn) and W_DISABLE2 (BT_RST)

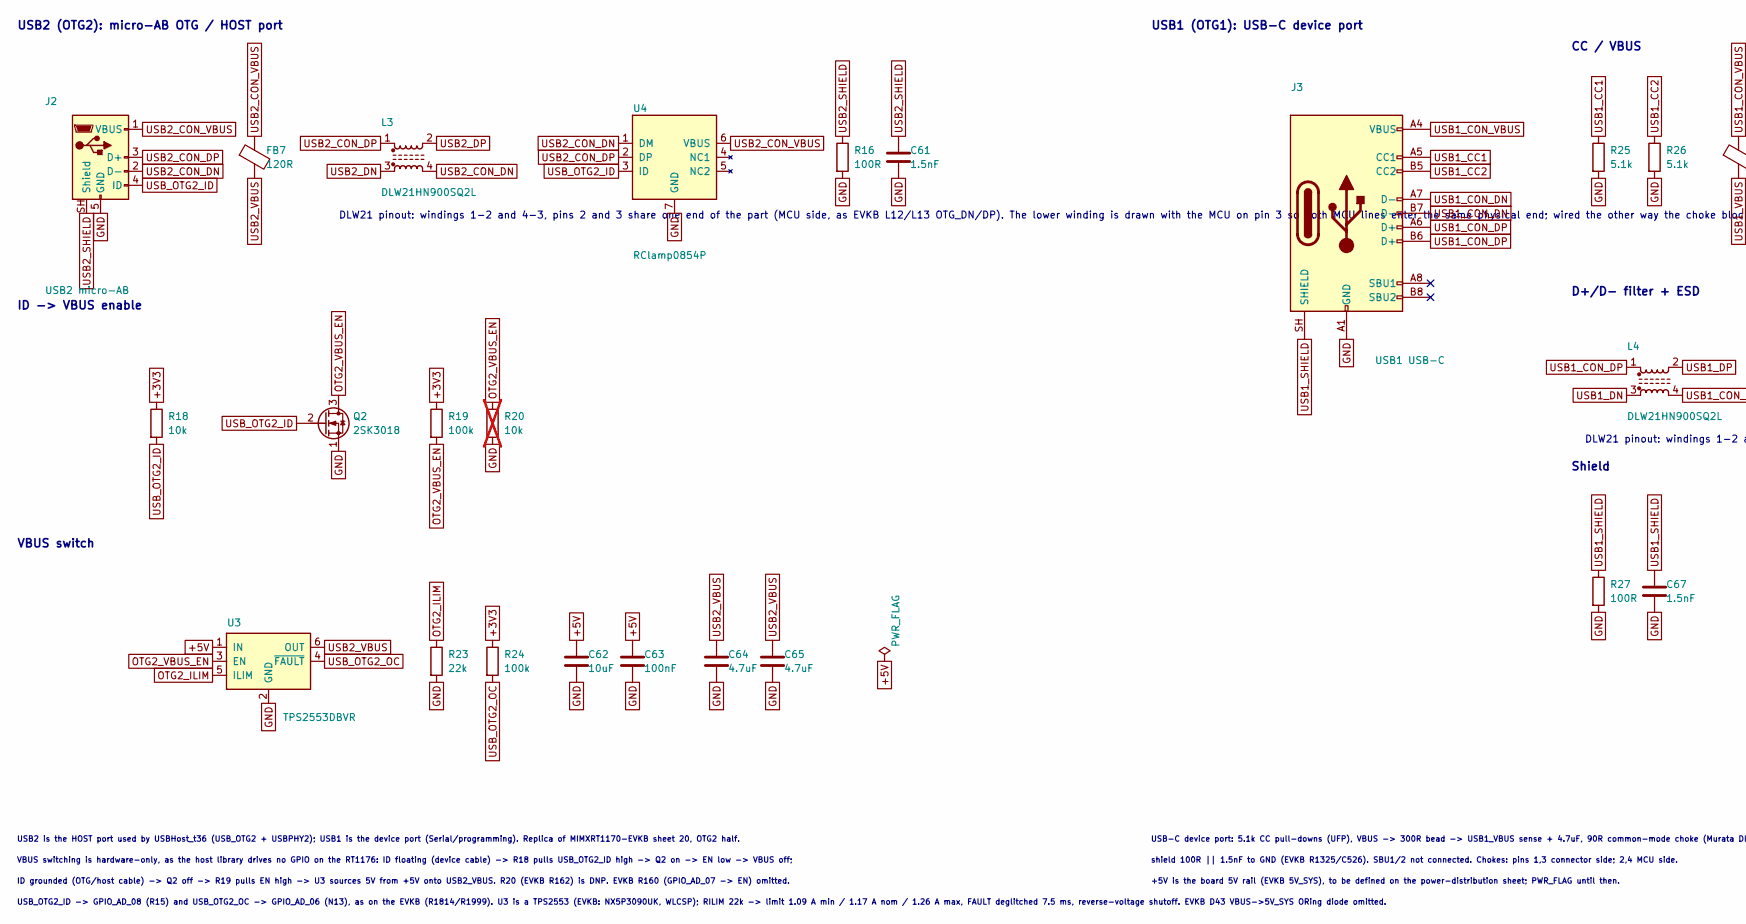
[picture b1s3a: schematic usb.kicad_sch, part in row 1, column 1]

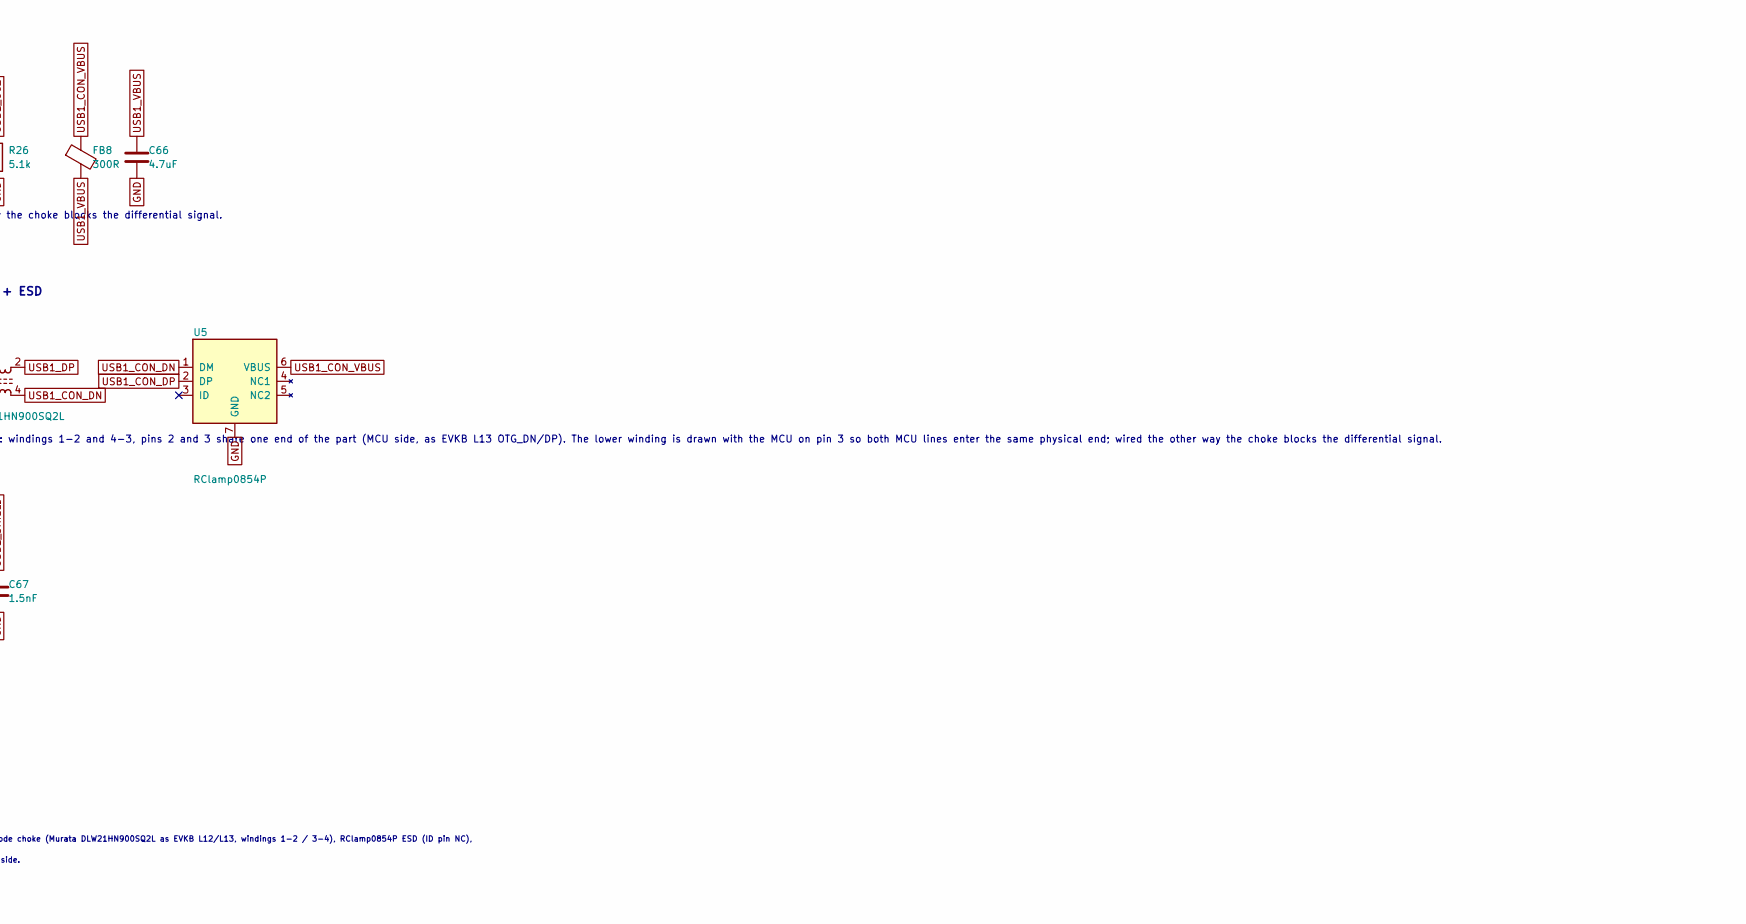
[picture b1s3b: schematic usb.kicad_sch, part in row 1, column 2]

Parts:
C61, C67: 1.5nF; C_0402_1005Metric_JLC; MPN CC0402KRX7R9BB152; LCSC C107022
C62: 10uF; C_0603_1608Metric; MPN CL10A106KP8NNNC; LCSC C19702
C63: 100nF; C_0402_1005Metric_JLC; MPN CL05B104KO5NNNC; LCSC C1525
C64, C65, C66: 4.7uF; C_0402_1005Metric_JLC; MPN CL05A475MP5NRNC; LCSC C23733
FB7: 120R; L_0603_1608Metric; MPN BLM18PG121SN1D; LCSC C14709
FB8: 300R; L_0603_1608Metric; MPN 742792641; LCSC C2649308
J2: USB2 micro-AB; USB_Micro-AB_Molex_47590-0001_JLC; MPN 47590-0001; LCSC C136001
J3: USB1 USB-C; USB_C_Receptacle_GCT_USB4105-xx-A_16P_TopMnt_Horizontal_JLC; MPN USB4105-GF-A-120; LCSC C5184243
L3, L4: DLW21HN900SQ2L; L_CommonModeChoke_Murata_DLW21; MPN DLW21HN900SQ2L; LCSC C80529
Q2: 2SK3018; SOT-323_SC-70; MPN 2SK3018T106; LCSC C113315
R16, R27: 100R; R_0402_1005Metric_JLC; MPN 0402WGF1000TCE; LCSC C25076
R18: 10k; R_0402_1005Metric_JLC; MPN 0402WGF1002TCE; LCSC C25744
R19, R24: 100k; R_0402_1005Metric_JLC; MPN 0402WGF1003TCE; LCSC C25741
R20: 10k; R_0402_1005Metric_JLC; MPN 0402WGF1002TCE; LCSC C25744; not fitted
R23: 22k; R_0402_1005Metric_JLC; MPN 0402WGF2202TCE; LCSC C25768
R25, R26: 5.1k; R_0402_1005Metric_JLC; MPN 0402WGF5101TCE; LCSC C25905
U3: TPS2553DBVR; SOT-23-6; MPN TPS2553DBVR; LCSC C55266
U4, U5: RClamp0854P; slp1616p6; MPN RCLAMP0854P.TCT; LCSC C842842

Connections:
+3V3: R18.1, R19.1, R24.1; also elsewhere on the board
+5V: C62.1, C63.1, U3.1 (IN); also elsewhere on the board
GND: C61.2, C62.2, C63.2, C64.2, C65.2, C66.2, C67.2, J2.5 (GND), J3.A1 (GND), J3.A12 (GND), J3.B1 (GND), J3.B12 (GND), Q2.1 (S), R16.2, R20.2, R23.2, R25.2, R26.2, R27.2, U3.2 (GND), U4.7 (GND), U5.7 (GND); also elsewhere on the board
OTG2_ILIM: R23.1, U3.5 (ILIM)
OTG2_VBUS_EN: Q2.3 (D), R19.2, R20.1, U3.3 (EN)
USB1_CC1: J3.A5 (CC1), R25.1
USB1_CC2: J3.B5 (CC2), R26.1
USB1_CON_DN: J3.A7 (D-), J3.B7 (D-), L4.4, U5.1 (DM)
USB1_CON_DP: J3.A6 (D+), J3.B6 (D+), L4.1, U5.2 (DP)
USB1_CON_VBUS: FB8.1, J3.A4 (VBUS), J3.A9 (VBUS), J3.B4 (VBUS), J3.B9 (VBUS), U5.6 (VBUS)
USB1_DN: L4.3; also elsewhere on the board
USB1_DP: L4.2; also elsewhere on the board
USB1_SHIELD: C67.1, J3.SH (SHIELD), R27.1
USB1_VBUS: C66.1, FB8.2; also elsewhere on the board
USB2_CON_DN: J2.2 (D-), L3.4, U4.1 (DM)
USB2_CON_DP: J2.3 (D+), L3.1, U4.2 (DP)
USB2_CON_VBUS: FB7.1, J2.1 (VBUS), U4.6 (VBUS)
USB2_DN: L3.3; also elsewhere on the board
USB2_DP: L3.2; also elsewhere on the board
USB2_SHIELD: C61.1, J2.SH (Shield), R16.1
USB2_VBUS: C64.1, C65.1, FB7.2, U3.6 (OUT); also elsewhere on the board
USB_OTG2_ID: J2.4 (ID), Q2.2 (G), R18.2, U4.3 (ID); also elsewhere on the board
USB_OTG2_OC: R24.2, U3.4 (~FAULT); also elsewhere on the board

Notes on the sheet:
ID grounded (OTG/host cable) -> Q2 off -> R19 pulls EN high -> U3 sources 5V from +5V onto USB2_VBUS. R20 (EVKB R162) is DNP. EVKB R160 (GPIO_AD_07 -> EN) omitted.
shield 100R || 1.5nF to GND (EVKB R1325/C526). SBU1/2 not connected. Chokes: pins 1,3 connector side; 2,4 MCU side.
USB1 (OTG1): USB-C device port
DLW21 pinout: windings 1-2 and 4-3, pins 2 and 3 share one end of the part (MCU side, as EVKB L13 OTG_DN/DP). The lower winding is drawn with the MCU on pin 3 so both MCU lines enter the same physical end; wired the other way the choke blocks the differential signal.
Shield
D+/D- filter + ESD
VBUS switch
+5V is the board 5V rail (EVKB 5V_SYS), to be defined on the power-distribution sheet; PWR_FLAG until then.
USB-C device port: 5.1k CC pull-downs (UFP), VBUS -> 300R bead -> USB1_VBUS sense + 4.7uF, 90R common-mode choke (Murata DLW21HN900SQ2L as EVKB L12/L13, windings 1-2 / 3-4), RClamp0854P ESD (ID pin NC),
CC / VBUS
USB_OTG2_ID -> GPIO_AD_08 (R15) and USB_OTG2_OC -> GPIO_AD_06 (N13), as on the EVKB (R1814/R1999). U3 is a TPS2553 (EVKB: NX5P3090UK, WLCSP); RILIM 22k -> limit 1.09 A min / 1.17 A nom / 1.26 A max, FAULT deglitched 7.5 ms, reverse-voltage shutoff. EVKB D43 VBUS->5V_SYS ORing diode omitted.
USB2 is the HOST port used by USBHost_t36 (USB_OTG2 + USBPHY2); USB1 is the device port (Serial/programming). Replica of MIMXRT1170-EVKB sheet 20, OTG2 half.
ID -> VBUS enable
VBUS switching is hardware-only, as the host library drives no GPIO on the RT1176: ID floating (device cable) -> R18 pulls USB_OTG2_ID high -> Q2 on -> EN low -> VBUS off;
DLW21 pinout: windings 1-2 and 4-3, pins 2 and 3 share one end of the part (MCU side, as EVKB L12/L13 OTG_DN/DP). The lower winding is drawn with the MCU on pin 3 so both MCU lines enter the same physical end; wired the other way the choke blocks the differential signal.
USB2 (OTG2): micro-AB OTG / HOST port

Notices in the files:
README.md:
`PWR_FLAG`s on passively fed rails. Sheet notes cite the EVKB reference designators for each
unchanged from [kicad-druid](https://github.com/Cimos/kicad-druid) (MIT licence, notice kept
